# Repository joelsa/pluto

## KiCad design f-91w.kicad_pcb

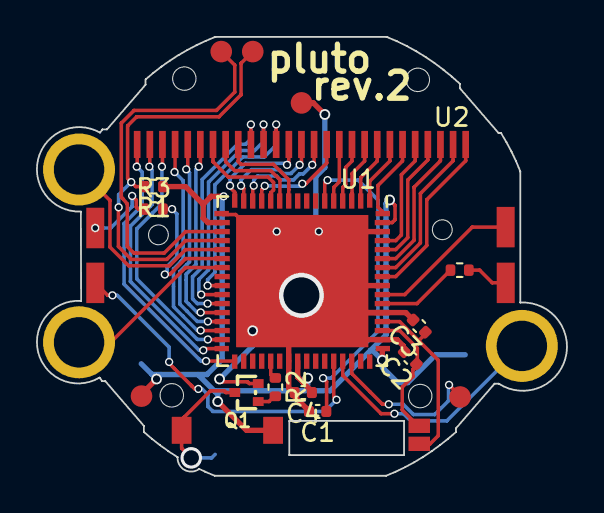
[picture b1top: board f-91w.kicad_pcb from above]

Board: 2 copper layers, 29.4 x 24.4 mm, 33 parts (0 on the bottom side), 47 nets.

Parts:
C1: 4.7u; C_0402_1005Metric
C2, C3: 22p; C_0402_1005Metric
C4: 100n; C_0402_1005Metric
MH1, MH2, MH3, MH4, MH5, MH6: 1pin
P1, P2, P3, P4, P5, P6, P7, P8, P9, P10, P11, P13, P14, P15: CONN_01X01; 1pin
P16, P17: CONN_01X01; LED
Q1: BC846; SOT416
R1: 10k; R_0402_1005Metric
R2: 47k; R_0402_1005Metric
R3, R101: 100; R_0402_1005Metric
U1: MSP430FR6972; QFN-64-1EP_9x9mm_Pitch0.5mm
U2: LCD-F-91W

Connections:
/BUZ: P9.1, Q1.3
/B_ALARM: P7.1, U1.45
/B_LIGHT: P5.1, U1.21
/B_MODE: P6.1, U1.23
/LCD_COM1: U1.12, U2.7
/LCD_COM2: U1.11, U2.8
/LCD_COM3: U1.10, U2.9
/LCD_SEG1: U1.33, U2.1
/LCD_SEG2: U1.32, U2.2
/LCD_SEG3: U1.31, U2.3
/LCD_SEG4: U1.30, U2.4
/LCD_SEG5: U1.29, U2.5
/LCD_SEG6: U1.28, U2.6
/LCD_SEG7: U1.27, U2.10
/LCD_SEG8: U1.26, U2.11
/LCD_SEG9: U1.25, U2.12
/LCD_SEG10: U1.16, U2.13
/LCD_SEG11: U1.15, U2.14
/LCD_SEG12: U1.14, U2.15
/LCD_SEG13: U1.13, U2.16
/LCD_SEG14: U1.5, U2.17
/LCD_SEG15: U1.4, U2.18
/LCD_SEG16: U1.3, U2.19
/LCD_SEG17: U1.2, U2.20
/LCD_SEG18: U1.1, U2.21
/LCD_SEG19: U1.64, U2.22
/LCD_SEG20: U1.61, U2.23
/LCD_SEG21: U1.60, U2.24
/LCD_SEG22: U1.59, U2.25
/LCD_SEG23: U1.58, U2.26
/LCD_SEG24: U1.57, U2.27
/LED_1: P11.1, U1.44
/LED_2: R3.2, U1.22
/LED_3: P16.1, U1.55
/LED_4: R101.2, U1.54
/Q-1: C2.1, P1.1, U1.51
/Q-2: C3.1, P2.1, U1.52
GND: C1.2, C2.2, C3.2, C4.2, P13.1, Q1.2, U1.17, U1.39, U1.50, U1.53, U1.56, U1.62, U1.65
unnamed: C1.1, U1.6
unnamed: P3.1, U1.19
unnamed: P4.1, R1.2, U1.20
unnamed: P10.1, R3.1
unnamed: P15.1, U1.46
unnamed: P17.1, R101.1
unnamed: Q1.1, R2.2
unnamed: R2.1, U1.37
VCC: C4.1, P8.1, P14.1, R1.1, U1.18, U1.40, U1.49, U1.63

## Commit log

2022-11-24 Add second LED, remove IR sensor
